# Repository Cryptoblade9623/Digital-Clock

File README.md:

# Digital-Clock
This is a digital clock that reflects the actual time in real life without you having to set it again.
It measures 30 x 85 x 85mm, so it is quite a compact device.
It does this by using a DS3231 module backed up by a CR2032 coin battery.
The time is displayed through a 7 segment 4 digit TM1637 module and a ring of WS2812B RGB lights that show the seconds.
It is powered by a 2000Mah battery with a J5019 charging and boost module and can be turned on and off with a 3 pin rocker switch.
It is a starter project from the [Half-Life YSWS](https://halflife.hackclub.com/dashboard).
I have changed it up by making it a fusion of 2 projects, using a different MCU and battery powering it.
The files include: 3D models of the case and PCB incase you want to make it yourself, PCB and schematics, BOM, firmware and gerber files.

## Pictures
Below are screenshots of the PCB, schematics, PCB rendering and case in Fusion 360.

## BOM
| Item                        | Qty | Supplier   | Cost/item | Total Cost | link                                                                                                                                                                                                                                                                                                                                                                                                                                                                                                                                                                                                                                                                                                                                                                                                                                                                                                                             |
|-----------------------------|-----|------------|-----------|------------|----------------------------------------------------------------------------------------------------------------------------------------------------------------------------------------------------------------------------------------------------------------------------------------------------------------------------------------------------------------------------------------------------------------------------------------------------------------------------------------------------------------------------------------------------------------------------------------------------------------------------------------------------------------------------------------------------------------------------------------------------------------------------------------------------------------------------------------------------------------------------------------------------------------------------------|
| Waveshare RP2040 - Zero     | 1   | AliExpress | $2.51     | $2.51      | https://www.aliexpress.com/item/1005005108143219.html?spm=a2g0o.productlist.main.7.3f1d1060BQNtc4&algo_pvid=e5476706-b173-4d7f-b254-8d702e27b734&algo_exp_id=e5476706-b173-4d7f-b254-8d702e27b734-6&pdp_ext_f=%7B%22order%22%3A%22142%22%2C%22spu_best_type%22%3A%22price%22%2C%22eval%22%3A%221%22%2C%22fromPage%22%3A%22search%22%7D&pdp_npi=6%40dis%21USD%212.51%212.50%21%21%212.51%212.50%21%4021038a9c17932159085441628e1100%2112000039019231334%21sea%21GB%210%21ABX%211%210%21n_tag%3A-29910%3Bd%3Ad6cd2d24%3Bm03_new_user%3A-29895%3BpisId%3A5000000218644952&curPageLogUid=s7GhyOkdsZ3a&utparam-url=scene%3Asearch%7Cquery_from%3A%7Cx_object_id%3A1005005108143219%7C_p_origin_prod%3A                                                                                                                                                                                                                                |
| 2000Mah Battery             | 1   | AliExpress | $5.99     | $5.99      | https://www.aliexpress.com/item/1005005614561610.html?spm=a2g0o.detail.pcDetailTopMoreOtherSeller.10.47f71UA91UA9tm&gps-id=pcDetailTopMoreOtherSeller&scm=1007.40050.354490.0&scm_id=1007.40050.354490.0&scm-url=1007.40050.354490.0&pvid=a5e69e93-03ff-41cb-8222-ed78d5e98786&_t=gps-id%3ApcDetailTopMoreOtherSeller%2Cscm-url%3A1007.40050.354490.0%2Cpvid%3Aa5e69e93-03ff-41cb-8222-ed78d5e98786%2Ctpp_buckets%3A668%232846%238111%231996&pdp_ext_f=%7B%22order%22%3A%22664%22%2C%22eval%22%3A%221%22%2C%22sceneId%22%3A%2230050%22%2C%22fromPage%22%3A%22recommend%22%7D&pdp_npi=6%40dis%21USD%215.99%211.35%21%21%215.99%211.35%21%40210381f017926611875426069e0e8c%2112000040028049695%21rec%21GB%21%21ABXZ%211%210%21n_tag%3A-29910%3Bd%3Ad6cd2d24%3Bm03_new_user%3A-29895%3BpisId%3A5000000218642852&utparam-url=scene%3ApcDetailTopMoreOtherSeller%7Cquery_from%3A%7Cx_object_id%3A1005005614561610%7C_p_origin_prod%3A |
| J5019 Module                | 1   | AliExpress | $1.37     | $1.37      | https://www.aliexpress.com/item/1005007352322912.html?spm=a2g0o.detail.pcDetailTopMoreOtherSeller.5.5c59qlPCqlPCO3&gps-id=pcDetailTopMoreOtherSeller&scm=1007.40050.354490.0&scm_id=1007.40050.354490.0&scm-url=1007.40050.354490.0&pvid=8298c1e3-9fae-4425-a7a4-18fcb9ff680c&_t=gps-id%3ApcDetailTopMoreOtherSeller%2Cscm-url%3A1007.40050.354490.0%2Cpvid%3A8298c1e3-9fae-4425-a7a4-18fcb9ff680c%2Ctpp_buckets%3A668%232846%238115%232000&pdp_ext_f=%7B%22order%22%3A%22123%22%2C%22eval%22%3A%221%22%2C%22sceneId%22%3A%2230050%22%2C%22fromPage%22%3A%22recommend%22%7D&pdp_npi=6%40dis%21USD%211.37%211.36%21%21%219.12%219.05%21%400b88a96117931162694441949e101b%2112000040388308945%21rec%21GB%21%21ABXZ%211%210%21n_tag%3A-29910%3Bd%3Ad6cd2d24%3Bm03_new_user%3A-29895%3BpisId%3A5000000218644952&utparam-url=scene%3ApcDetailTopMoreOtherSeller%7Cquery_from%3A%7Cx_object_id%3A1005007352322912%7C_p_origin_prod%3A  |
| DS3231 Module               | 1   | AliExpress | $1.56     | $1.56      | https://www.aliexpress.com/item/1005013442131879.html?spm=a2g0o.detail.similar_items.3.7526IMntIMntQQ&utparam-url=scene%3Aimage_search%7Cquery_from%3Aapp_pdp_sold_out%7Cx_object_id%3A1005013442131879%7C_p_origin_prod%3A&algo_pvid=7136bc9e-633b-4398-af18-21c6d25cc6b9&algo_exp_id=7136bc9e-633b-4398-af18-21c6d25cc6b9&pdp_ext_f=%7B%22order%22%3A%22-1%22%2C%22fromPage%22%3A%22search%22%7D&pdp_npi=6%40dis%21USD%2112.48%211.56%21%21%2182.82%2110.33%21%402161390617931137931526660e0ed1%2112000061138015019%21sea%21GB%210%21ABX%211%210%21n_tag%3A-29910%3Bd%3Ad6cd2d24%3Bm03_new_user%3A-29895#nav-specification                                                                                                                                                                                                                                                                                                     |
| TM1637 Module               | 1   | AliExpress | $1.21     | $1.21      | https://www.aliexpress.com/item/1005008658129354.html?spm=a2g0o.productlist.main.55.3e63f0eaxAx49V&algo_pvid=8ff6008d-0146-464a-92ee-a2c00a96c52b&algo_exp_id=8ff6008d-0146-464a-92ee-a2c00a96c52b-52&pdp_ext_f=%7B%22order%22%3A%2223%22%2C%22spu_best_type%22%3A%22price%22%2C%22eval%22%3A%221%22%2C%22fromPage%22%3A%22search%22%7D&pdp_npi=6%40dis%21USD%211.21%211.21%21%21%211.21%211.21%21%400b884a9917931151212464144e0d49%2112000046124502768%21sea%21GB%210%21ABX%211%210%21n_tag%3A-29910%3Bd%3Ad6cd2d24%3Bm03_new_user%3A-29895&curPageLogUid=1sDXgWB6cZBK&utparam-url=scene%3Asearch%7Cquery_from%3A%7Cx_object_id%3A1005008658129354%7C_p_origin_prod%3A#nav-specification                                                                                                                                                                                                                                        |
| WS2812B RGB Lights          | 1   | AliExpress | $1.57     | $1.57      | https://www.aliexpress.com/item/1005001376489095.html?spm=a2g0o.productlist.main.9.793778d09XBn7Y&algo_pvid=630078d6-5b43-4267-a8db-f424a7e97089&algo_exp_id=630078d6-5b43-4267-a8db-f424a7e97089-8&pdp_ext_f=%7B%22order%22%3A%22191%22%2C%22eval%22%3A%221%22%2C%22fromPage%22%3A%22search%22%7D&pdp_npi=6%40dis%21USD%211.54%211.53%21%21%2110.19%2110.12%21%400b88a95617931131393632374e0fc5%2112000029992995671%21sea%21GB%210%21ABX%211%210%21n_tag%3A-29910%3Bd%3Ad6cd2d24%3Bm03_new_user%3A-29895%3BpisId%3A5000000218644952&curPageLogUid=Ney67dBOepAl&utparam-url=scene%3Asearch%7Cquery_from%3A%7Cx_object_id%3A1005001376489095%7C_p_origin_prod%3A                                                                                                                                                                                                                                                                  |
| 100nF Capcitors             | 1   | AliExpress | $1.28     | $1.28      | https://www.aliexpress.com/item/1005007533532838.html?spm=a2g0o.productlist.main.9.2f294f4bMSIl03&algo_pvid=4a059cae-29c6-4d92-aa86-a28a010e07e4&algo_exp_id=4a059cae-29c6-4d92-aa86-a28a010e07e4-8&pdp_ext_f=%7B%22order%22%3A%22133%22%2C%22eval%22%3A%221%22%2C%22fromPage%22%3A%22search%22%7D&pdp_npi=6%40dis%21USD%211.28%211.28%21%21%218.51%218.51%21%402161390617931181600818168e0c50%2112000041188037343%21sea%21GB%210%21ABX%211%210%21n_tag%3A-29910%3Bd%3Ad6cd2d24%3Bm03_new_user%3A-29895&curPageLogUid=ygSORZkpai6h&utparam-url=scene%3Asearch%7Cquery_from%3A%7Cx_object_id%3A1005007533532838%7C_p_origin_prod%3A                                                                                                                                                                                                                                                                                               |
| 1000uF Capacitor + Shipping | 1   | Alibaba    | $0.49     | $0.49      | https://www.alibaba.com/product-detail/SeekEC-35v-1000uf-Imported-Electrolytic-Capacitor_10000047487804.html?spm=a2756.trade-carp.valid-supplier.2.6a403192KqLRKB                                                                                                                                                                                                                                                                                                                                                                                                                                                                                                                                                                                                                                                                                                                                                                |
| SN74AHCT1G125DBVR           | 1   | AliExpress | $3.14     | $3.14      | https://www.aliexpress.com/item/1005006207262483.html?spm=a2g0o.productlist.main.1.17cb7105tepdGv&algo_pvid=fe78a278-3c04-4196-9bdb-2f9d6d9721a9&algo_exp_id=fe78a278-3c04-4196-9bdb-2f9d6d9721a9-0&pdp_ext_f=%7B%22order%22%3A%2255%22%2C%22eval%22%3A%221%22%2C%22fromPage%22%3A%22search%22%7D&pdp_npi=6%40dis%21USD%213.14%213.13%21%21%2120.82%2120.75%21%400b88ab6717931259590427833e0f17%2112000045075843953%21sea%21GB%210%21ABX%211%210%21n_tag%3A-29910%3Bd%3Ad6cd2d24%3Bm03_new_user%3A-29895%3BpisId%3A5000000218644952&curPageLogUid=3Hg7hSheoOGg&utparam-url=scene%3Asearch%7Cquery_from%3A%7Cx_object_id%3A1005006207262483%7C_p_origin_prod%3A                                                                                                                                                                                                                                                                   |
| 330Ω Resistor               | 1   | AliExpress | $1.04     | $1.04      | https://www.aliexpress.com/item/1005008971731418.html?spm=a2g0o.productlist.main.9.711a62fb6OeOLB&algo_pvid=3066dfb9-ede2-4be7-8da2-9b8f3dfc9233&algo_exp_id=3066dfb9-ede2-4be7-8da2-9b8f3dfc9233-38&pdp_ext_f=%7B%22order%22%3A%22201%22%2C%22eval%22%3A%221%22%2C%22fromPage%22%3A%22search%22%7D&pdp_npi=6%40dis%21USD%210.93%210.93%21%21%216.18%216.18%21%400b0fe40d17931968157764342e0d87%2112000047414565903%21sea%21GB%210%21ABX%211%210%21n_tag%3A-29910%3Bd%3Ad6cd2d24%3Bm03_new_user%3A-29895&curPageLogUid=kHgK7Ns7Mhot&utparam-url=scene%3Asearch%7Cquery_from%3A%7Cx_object_id%3A1005008971731418%7C_p_origin_prod%3A                                                                                                                                                                                                                                                                                              |
| Custom PCB ( Pack of 5 )    | 1   | JLCPCB     | $4.00     | $4.00      | https://cart.jlcpcb.com/quote?spm=Jlcpcb.Homepage.1006&spm=Jlcpcb.Homepage.1006&spm=Jlcpcb.Instantquote.1008&_t=1793396036865&up_spm=Jlcpcb.Loginpage.1003                                                                                                                                                                                                                                                                                                                                                                                                                                                                                                                                                                                                                                                                                                                                                                       |
| Estimated total shipping    |     |            |           | $4.95      |                                                                                                                                                                                                                                                                                                                                                                                                                                                                                                                                                                                                                                                                                                                                                                                                                                                                                                                                  |
| Grand Total                 |     |            |           | $29.11     |                                                                                                                                                                                                                                                                                                                                                                                                                                                                                                                                                                                                                                                                                                                                                                                                                                                                                                                                  |

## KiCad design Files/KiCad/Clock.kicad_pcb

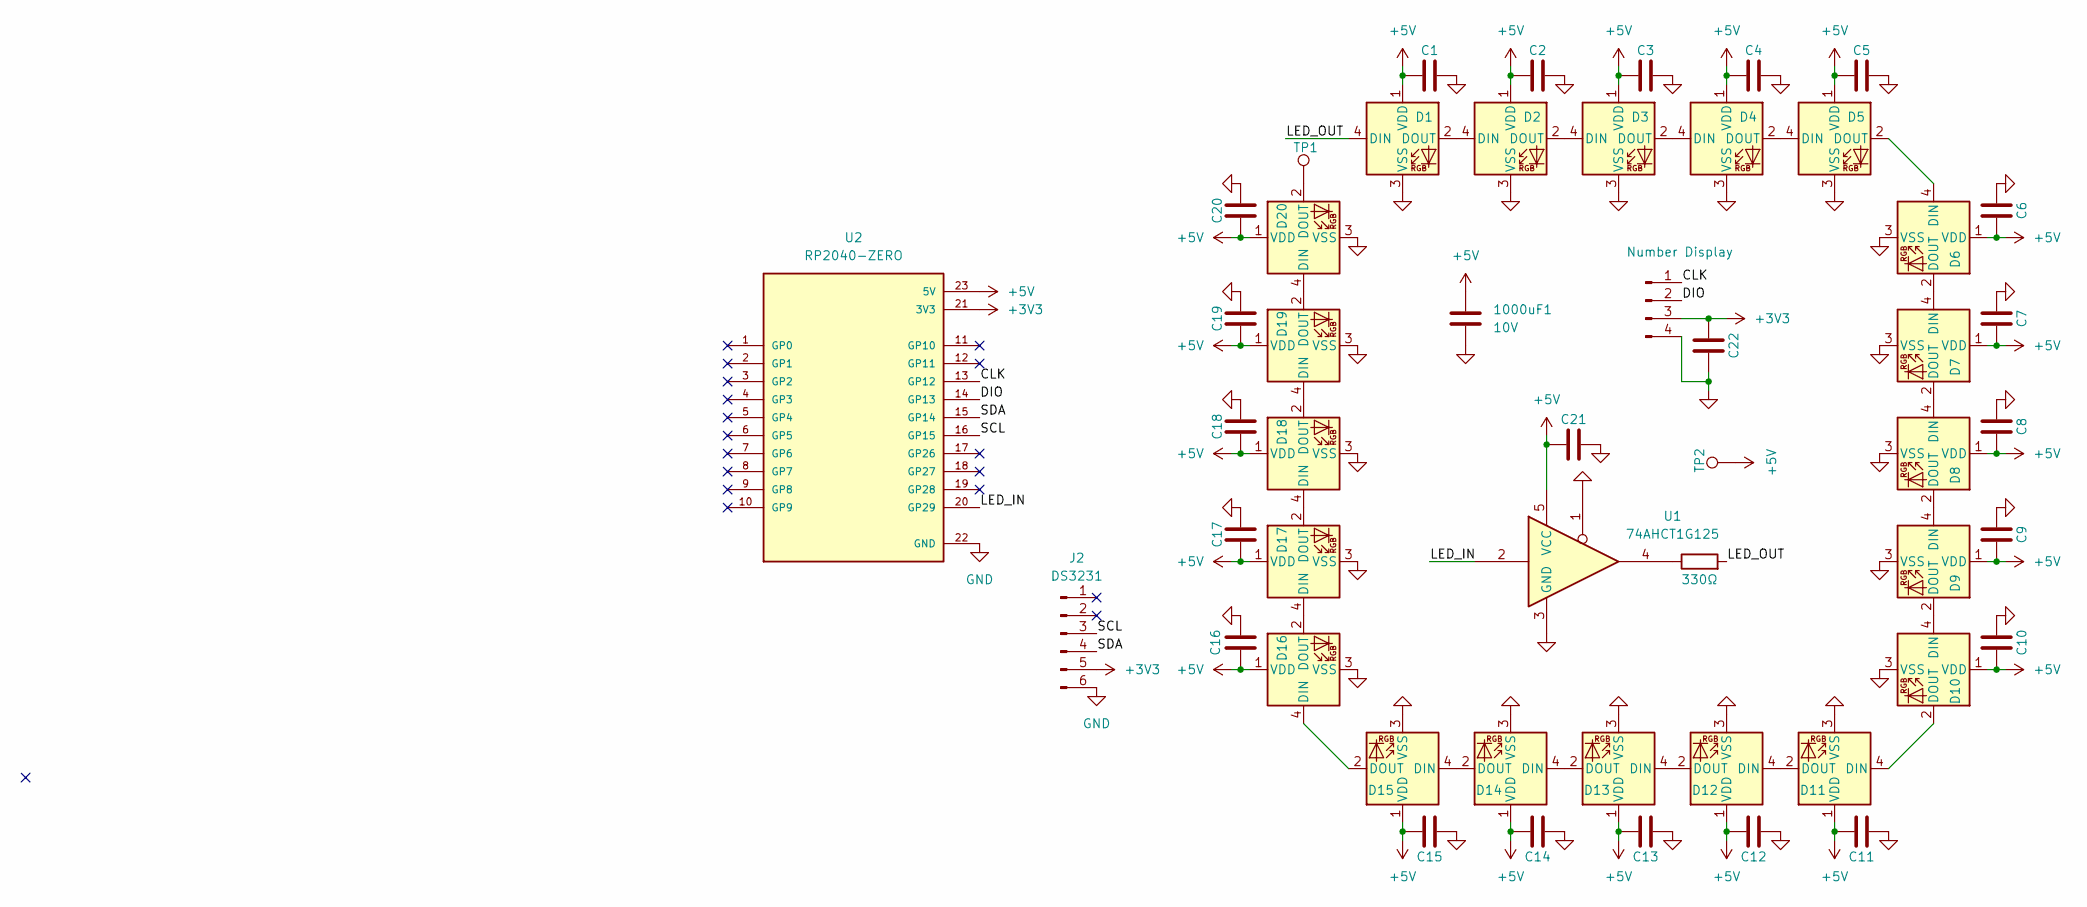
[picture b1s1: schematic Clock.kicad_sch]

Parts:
1000uF1: 10V; C_Radial_D12.5mm_H25.0mm_P5.00mm
C1, C2, C3, C4, C5, C6, C7, C8, C9, C10, C11, C12, C13, C14, C15, C16, C17, C18, C19, C20, C21, C22: C; C_0805_2012Metric_Pad1.18x1.45mm_HandSolder
D1, D2, D3, D4, D5, D6, D7, D8, D9, D10, D11, D12, D13, D14, D15, D16, D17, D18, D19, D20: WS2812B; LED_WS2812B_PLCC4_5.0x5.0mm_P3.2mm
J1: Number Display; TM1637_4PIN_Module
J2: DS3231; Untitled_1
R1: 330Ω; R_1206_3216Metric_Pad1.30x1.75mm_HandSolder
TP1, TP2: TestPoint; TestPoint_Pad_4.0x4.0mm
U1: 74AHCT1G125; SOT-23-5_HandSoldering
U2: RP2040-ZERO; MODULE_RP2040-ZERO; PARTREV NA

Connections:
+3V3: C22.1, J1.3, J2.5, U2.21 (3V3)
+5V: 1000uF1.1, C1.1, C2.1, C3.1, C4.1, C5.1, C6.2, C7.2, C8.2, C9.2, C10.2, C11.2, C12.2, C13.2, C14.2, C15.2, C16.2, C17.2, C18.2, C19.2, C20.2, C21.1, D1.1 (VDD), D2.1 (VDD), D3.1 (VDD), D4.1 (VDD), D5.1 (VDD), D6.1 (VDD), D7.1 (VDD), D8.1 (VDD), D9.1 (VDD), D10.1 (VDD), D11.1 (VDD), D12.1 (VDD), D13.1 (VDD), D14.1 (VDD), D15.1 (VDD), D16.1 (VDD), D17.1 (VDD), D18.1 (VDD), D19.1 (VDD), D20.1 (VDD), TP2.1 (1_1), U1.5 (VCC), U2.23 (5V)
/CLK: J1.1, U2.13 (GP12)
/DIO: J1.2, U2.14 (GP13)
/LED_IN: U1.2, U2.20 (GP29)
/LED_OUT: D1.4 (DIN), R1.2
/SCL: J2.3, U2.16 (GP15)
/SDA: J2.4, U2.15 (GP14)
GND: 1000uF1.2, C1.2, C2.2, C3.2, C4.2, C5.2, C6.1, C7.1, C8.1, C9.1, C10.1, C11.1, C12.1, C13.1, C14.1, C15.1, C16.1, C17.1, C18.1, C19.1, C20.1, C21.2, C22.2, D1.3 (VSS), D2.3 (VSS), D3.3 (VSS), D4.3 (VSS), D5.3 (VSS), D6.3 (VSS), D7.3 (VSS), D8.3 (VSS), D9.3 (VSS), D10.3 (VSS), D11.3 (VSS), D12.3 (VSS), D13.3 (VSS), D14.3 (VSS), D15.3 (VSS), D16.3 (VSS), D17.3 (VSS), D18.3 (VSS), D19.3 (VSS), D20.3 (VSS), J1.4, J2.6, U1.1, U1.3 (GND), U2.22 (GND)
unnamed: D1.2 (DOUT), D2.4 (DIN)
unnamed: D2.2 (DOUT), D3.4 (DIN)
unnamed: D3.2 (DOUT), D4.4 (DIN)
unnamed: D4.2 (DOUT), D5.4 (DIN)
unnamed: D5.2 (DOUT), D6.4 (DIN)
unnamed: D6.2 (DOUT), D7.4 (DIN)
unnamed: D7.2 (DOUT), D8.4 (DIN)
unnamed: D8.2 (DOUT), D9.4 (DIN)
unnamed: D9.2 (DOUT), D10.4 (DIN)
unnamed: D10.2 (DOUT), D11.4 (DIN)
unnamed: D11.2 (DOUT), D12.4 (DIN)
unnamed: D12.2 (DOUT), D13.4 (DIN)
unnamed: D13.2 (DOUT), D14.4 (DIN)
unnamed: D14.2 (DOUT), D15.4 (DIN)
unnamed: D15.2 (DOUT), D16.4 (DIN)
unnamed: D16.2 (DOUT), D17.4 (DIN)
unnamed: D17.2 (DOUT), D18.4 (DIN)
unnamed: D18.2 (DOUT), D19.4 (DIN)
unnamed: D19.2 (DOUT), D20.4 (DIN)
unnamed: D20.2 (DOUT), TP1.1 (1_1)
unnamed: R1.1, U1.4

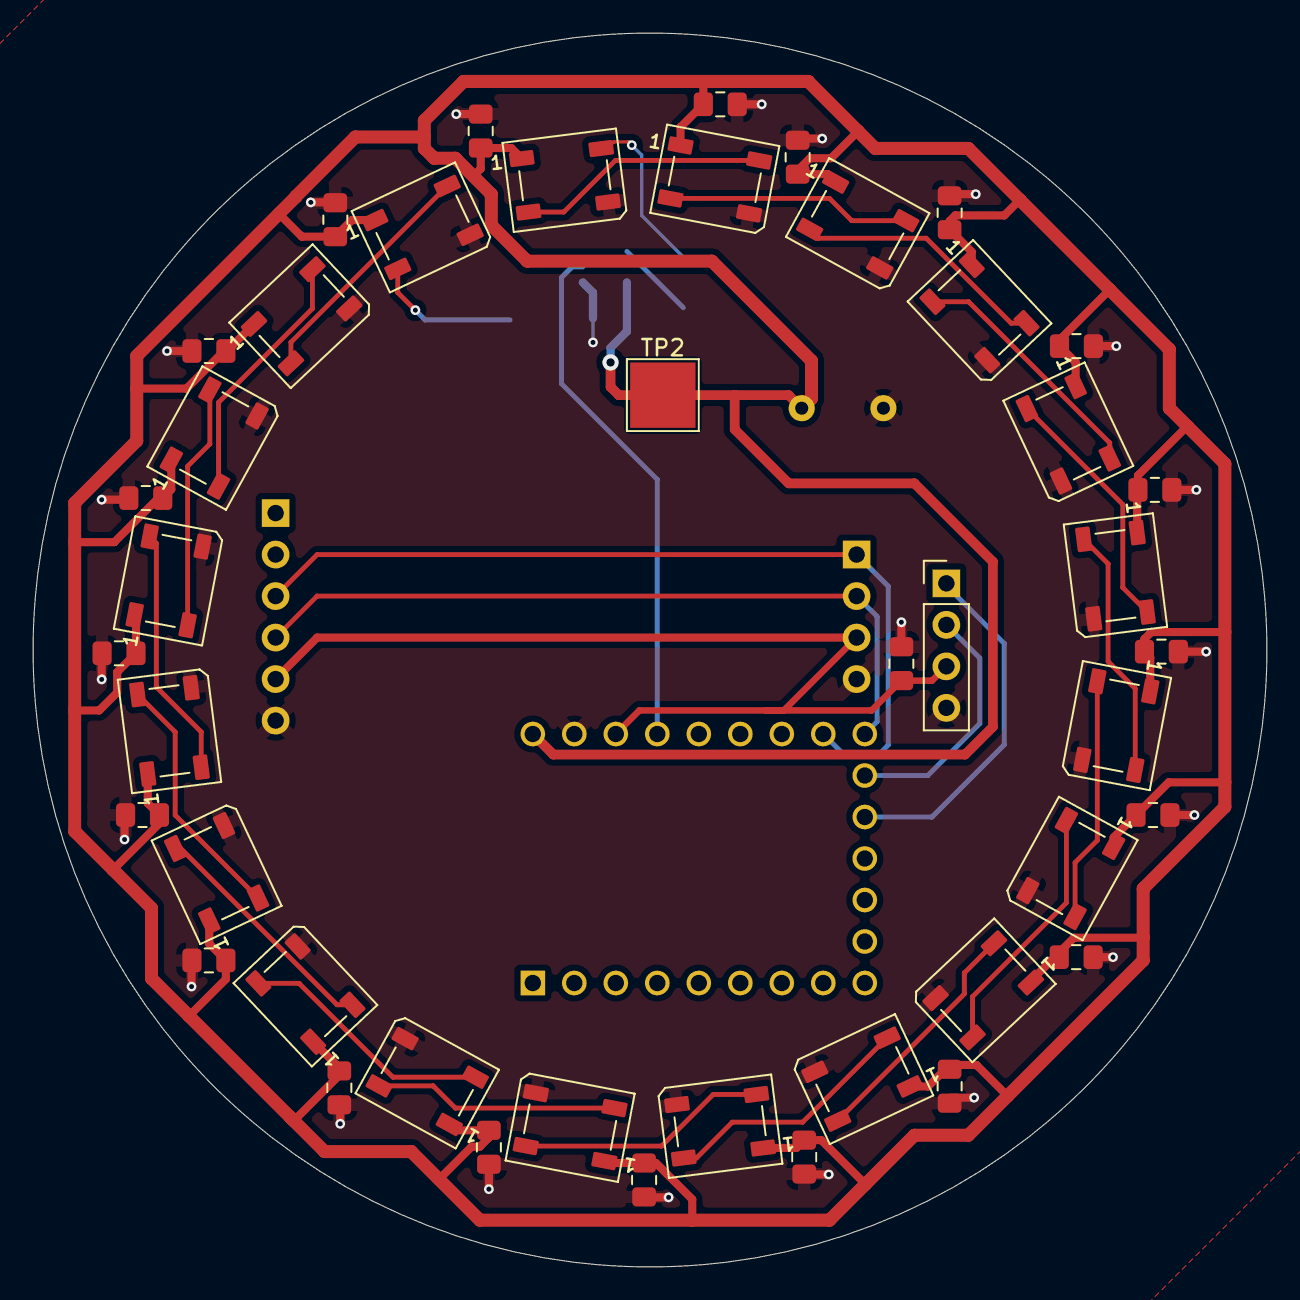
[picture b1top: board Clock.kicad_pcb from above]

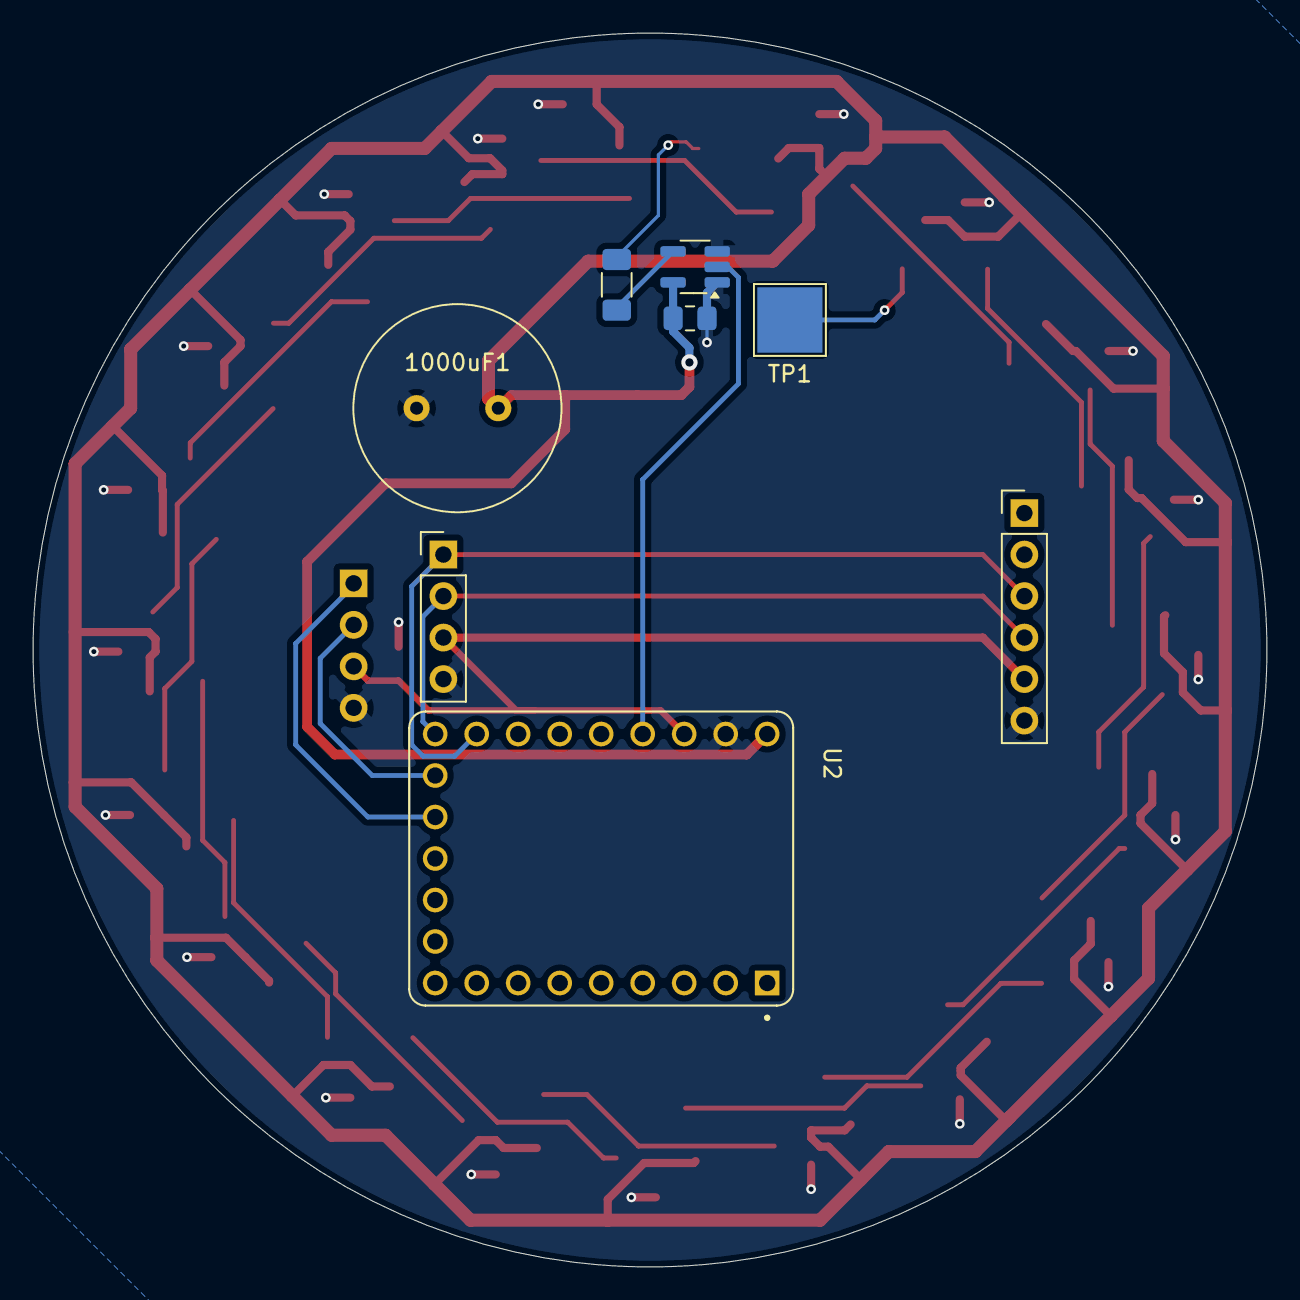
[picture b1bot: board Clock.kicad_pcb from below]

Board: 2 copper layers, 75.5 x 75.5 mm, 50 parts (7 on the bottom side), 30 nets.

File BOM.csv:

Item,Qty,Supplier,Cost/item,Total Cost,link
Waveshare RP2040 - Zero,1,AliExpress,$2.51,$2.51,https://www.aliexpress.com/item/1005005108143219.html?spm=a2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
2000Mah Battery,1,AliExpress,$5.99,$5.99,https://www.aliexpress.com/item/1005005614561610.html?spm=a2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
TP4056 Charging & Boost Module,1,AliExpress,$1.37,$1.37,https://www.aliexpress.com/item/1005007352322912.html?spm=a2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
DS3231 Module,1,AliExpress,$1.56,$1.56,https://www.aliexpress.com/item/1005013442131879.html?spm=a2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
TM1637 Module,1,AliExpress,$1.21,$1.21,https://www.aliexpress.com/item/1005008658129354.html?spm=a2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
WS2812B RGB Lights,1,AliExpress,$1.57,$1.57,https://www.aliexpress.com/item/1005001376489095.html?spm=a2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
100nF Capcitors,1,AliExpress,$1.28,$1.28,https://www.aliexpress.com/item/1005007533532838.html?spm=a2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
1000uF Capacitor + Shipping,1,Alibaba,$0.49,$0.49,https://www.alibaba.com/product-detail/SeekEC-35v-1000uf-Imp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
SN74AHCT1G125DBVR,1,AliExpress,$3.14,$3.14,https://www.aliexpress.com/item/1005006207262483.html?spm=a2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
330Ω Resistor,1,AliExpress,$1.04,$1.04,https://www.aliexpress.com/item/1005008971731418.html?spm=a2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
Estimated total shipping,1,,,$0.00,
